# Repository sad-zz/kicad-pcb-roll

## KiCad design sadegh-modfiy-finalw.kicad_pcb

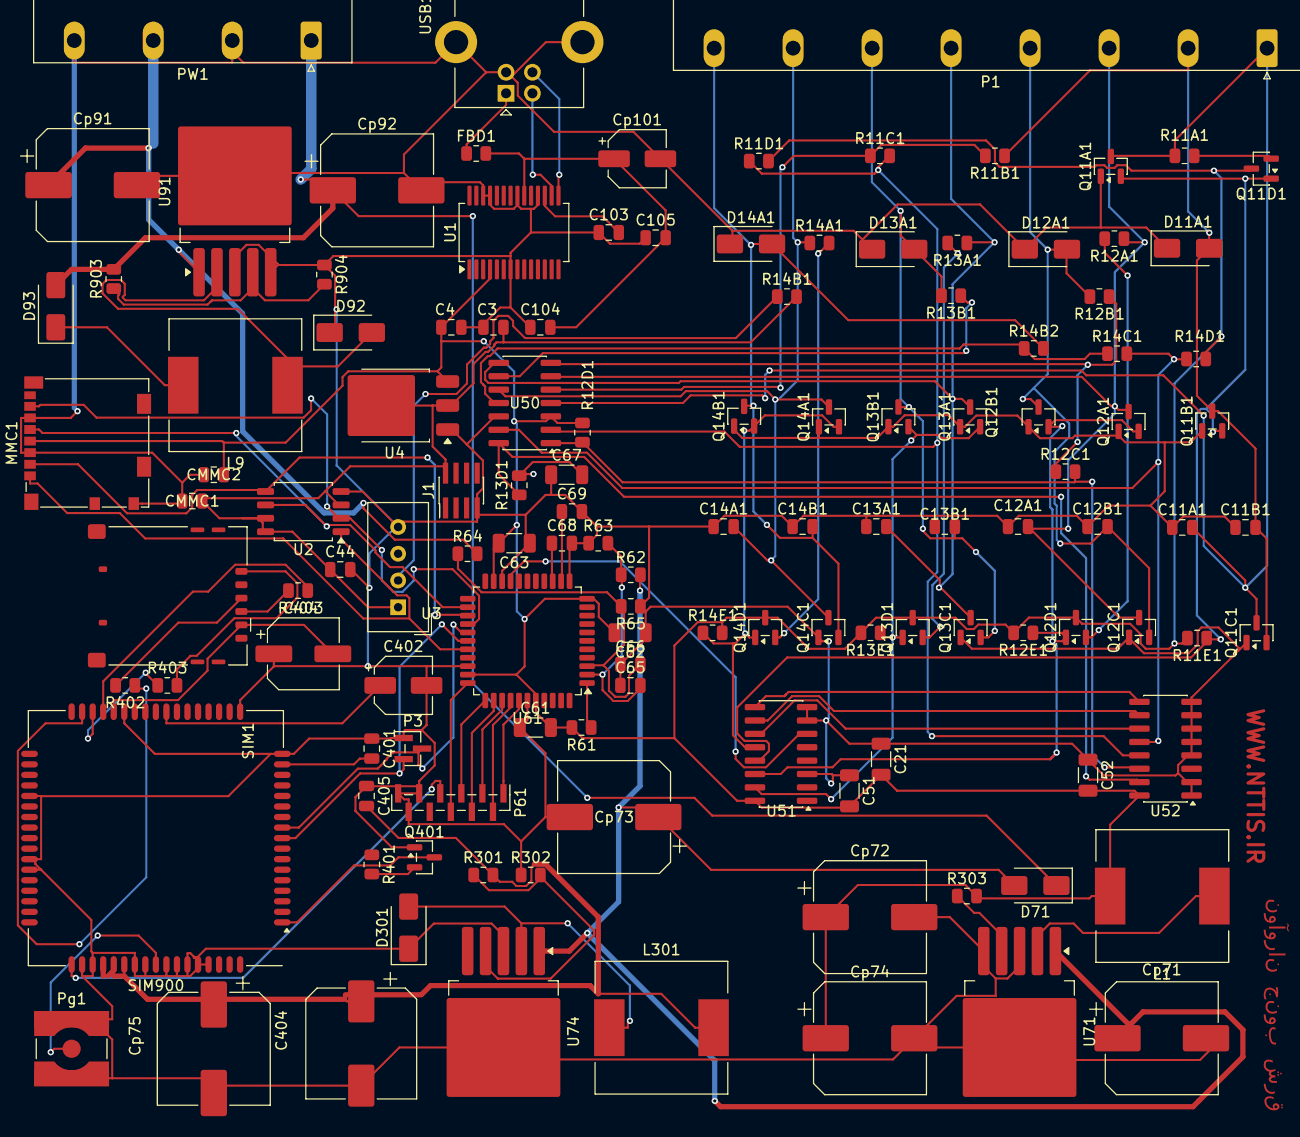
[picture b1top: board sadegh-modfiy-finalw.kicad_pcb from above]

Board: 2 copper layers, 124 parts (0 on the bottom side), 78 nets.

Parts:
C3, C4, C11A1, C11B1, C12A1, C12B1, C13A1, C13B1, C14A1, C14B1, C44, C65, C66, C68, C69, C103, C104, C105, C401, C405: Cap; C_0805_2012Metric
C21, C51, C52, C61, C62, C63, C67: Cap; C_1206_3216Metric
C402: Cap Pol1; CP_Elec_5x5.3
C403: Cap; CP_Elec_6.3x5.4
C404: Cap Pol1; CP_Elec_10x10
CMMC1, CMMC2: Cap; C_0805_2012Metric
Cp71, Cp72, Cp73, Cp74, Cp75, Cp91, Cp92: Cap Pol1; CP_Elec_10x12.5
Cp101: Cap Pol1; CP_Elec_5x5.3
D11A1, D12A1, D13A1, D14A1: 1N5819; D_SMA
D71: Diode 1N4007; D_SMA
D92, D301: Diode 1N5819; D_SMA
D93: Diode 1N4001; D_SMA
FBD1: Res1; R_0805_2012Metric
J1: Conn_02x04_Odd_Even; PinHeader_2x04_P1.00mm_Vertical_SMD
L1, L9, L301: Inductor Iron; L_12x12mm_H8mm
MMC1: MMC/SD; microSD_HC_Molex_104031-0811
P1: Header 8; PhoenixContact_GMSTBA_2,5_8-G_1x08_P7.50mm_Horizontal
P3: Header 3; PinHeader_1x03_P1.00mm_Vertical_SMD_Pin1Left
P61: Header 11; PinHeader_1x11_P1.00mm_Vertical_SMD_Pin1Left
PW1: Header 4; PhoenixContact_GMSTBA_2,5_4-G_1x04_P7.50mm_Horizontal
Pg1: SMB; SMA_Amphenol_132134-10_Vertical
Q11A1, Q11B1, Q11C1, Q12A1, Q12B1, Q12C1, Q13A1, Q13B1, Q13C1, Q14A1, Q14B1, Q14C1: 2N7000; SOT-23
Q11D1, Q12D1, Q13D1, Q14D1: 2SJ196/BSS92; SOT-23
Q401: 2N3904; SOT-23
R11A1, R11B1, R11C1, R11D1, R11E1, R12A1, R12B1, R12C1, R12D1, R12E1, R13A1, R13B1, R13D1, R13E1, R14A1, R14B1, R14B2, R14C1, R14D1, R14E1, R61, R62, R63, R64, R65, R301, R302, R303, R401, R903, R904: Res1; R_0805_2012Metric
R402, R403, R404: R_0805_2012Metric
SIM1: 6PIN SIMCARD; microSIM_JAE_SF53S006VCBR2000
SIM900: SIM900/SIM900A; SIMCom_SIM900
U1: UART<->USB; SSOP-28_5.3x10.2mm_P0.65mm
U2: W25Q32JVSS; SOIC-8_5.3x5.3mm_P1.27mm
U3: DHT11; Aosong_DHT11_5.5x12.0_P2.54mm
U4: AMS1117CD-3.3; TO-252-3_TabPin2
U50: LM339J; SOIC-14_3.9x8.7mm_P1.27mm
U51, U52: HCF4051BEY; SOIC-16_3.9x9.9mm_P1.27mm
U61: DSPIC30F4011-30I/P; TQFP-44_10x10mm_P0.8mm
U71, U74, U91: LM2576D2T-ADJ; TO-263-5_TabPin3
USB1: USB TYPEB; USB_B_Lumberg_2411_02_Horizontal

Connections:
/MISO: MMC1.7 (MISO), U2.2 (DO/IO_{1}), U61.26 (PGC/EMUC/U1RX/SDI1/SDA/RF2)
/MMCCS: MMC1.1 (CS), U2.1 (~CS), U61.29 (C1TX/RF1)
/MOSI: MMC1.2 (MOSI), U2.5 (DI/IO_{0}), U61.25 (PGD/EMUD/U1TX/SDO1/SCL/RF3)
/NetLight: P61.7, SIM900.52 (NETLIGHT)
/SCK: MMC1.5 (SCK), U2.6 (CLK), U61.24 (SCK1/RF6)
/SIM900_RXD: P3.2, SIM900.10 (RXD), U61.27 (U2TX/CN18/RF5)
/SIM900_TXD: P3.3, SIM900.9 (TXD), U61.28 (U2RX/CN17/RF4)
/loopselA: U51.11 (A), U52.11 (A)
/loopselB: U51.10 (B), U52.10 (B)
/loopselC: U51.9 (C), U52.9 (C)
GND: C3.1, C4.2, C11A1.1, C11B1.1, C12A1.1, C12B1.1, C13A1.1, C13B1.1, C14A1.1, C14B1.1, C21.1, C44.2, C51.1, C52.1, C61.1, C62.1, C63.1, C65.1, C66.1, C67.1, C68.2, C69.2, C103.1, C104.1, C105.1, C401.1, C402.2, C403.1, C404.2, C405.1, CMMC1.1, CMMC2.1, Cp71.2, Cp72.2, Cp73.2, Cp74.2, Cp75.2, Cp91.2, Cp92.2, Cp101.2, D11A1.1 (A), D12A1.1 (A), D13A1.1 (A), D14A1.1 (A), D92.1 (A), D301.1 (A), J1.7, MMC1.3 (GND), MMC1.6 (GND), MMC1.10 (HOLDER), P3.1, P61.9, P61.10, P61.11, PW1.2, PW1.4, Pg1.2 (Y), Q11A1.1 (E), Q11B1.1 (E), Q11C1.1 (E), Q12A1.1 (E), Q12B1.1 (E), Q12C1.1 (E), Q13A1.1 (E), Q13B1.1 (E), Q13C1.1 (E), Q14A1.1 (E), Q14B1.1 (E), Q14C1.1 (E), Q401.1 (E), R63.1, R65.1, R302.1, R904.1, SIM900.17 (GND), SIM900.18 (GND), SIM900.29 (GND), SIM900.39 (GND), SIM900.45 (GND), SIM900.46 (GND), SIM900.53 (GND), SIM900.54 (GND), SIM900.58 (GND), SIM900.59 (GND), SIM900.61 (GND), SIM900.62 (GND), SIM900.63 (GND), SIM900.64 (GND), SIM900.65 (GND), U1.7 (GND), U1.18 (GND), U1.21 (GND), U1.25 (AGND), U1.26 (TEST), U2.4 (GND), U3.4 (GND), U4.1 (GND), U50.12 (GND), U51.3 (IO_COM), U51.7 (GND), U51.8 (GND), U52.1 (IO_4), U52.2 (IO_6), U52.4 (IO_7), U52.5 (IO_5), U52.6 (INH), U52.7 (GND), U52.8 (GND), U61.12 (VSS), U61.20 (VSS), U61.31 (VSS), U61.39 (AVSS), U71.3 (GND), U71.5 (~ON/OFF), U74.3 (GND), U91.3 (GND), U91.5 (~ON/OFF), USB1.4 (GND), USB1.5 (HOLDER)
unnamed: C402.1, SIM900.25
unnamed: C11B1.2, D11A1.2 (K), P1.2, Q11B1.3 (C), Q11C1.2 (B), R11B1.1
unnamed: C12B1.2, D12A1.2 (K), P1.4, Q12B1.3 (C), Q12C1.2 (B), R12B1.2
unnamed: C13B1.2, D13A1.2 (K), P1.6, Q13B1.3 (C), Q13C1.2 (B), R13B1.2
unnamed: C14B1.2, D14A1.2 (K), P1.8, Q14B1.3 (C), Q14C1.2 (B), R14B2.2
unnamed: L1.1, U71.2 (OUT)
unnamed: D92.2 (K), L9.1, U91.2 (OUT)
unnamed: D93.1 (A), L9.2
unnamed: D301.2 (K), L301.1, U74.2 (OUT)
unnamed: C3.2, C44.1, CMMC1.2, J1.2, R14B1.2, U2.3 (~WP/IO_{2}), U2.7 (~HOLD/~RESET/IO_{3}), U2.8 (VCC), U3.1 (VDD), U4.2 (VO)
unnamed: Pg1.1 (X), SIM900.60 (RF_ANT)
unnamed: Q11A1.2 (B), Q11B1.2 (B), Q11D1.1 (G), R11E1.1, U51.13 (IO_0)
unnamed: C11A1.2, P1.1, Q11A1.3 (C), Q11C1.3 (C), R11A1.1, U50.4 (IN1-)
unnamed: Q11D1.2 (D), R11A1.2
unnamed: Q12A1.2 (B), Q12B1.2 (B), Q12D1.1 (G), R12E1.1, U51.14 (IO_1)
unnamed: C12A1.2, P1.3, Q12A1.3 (C), Q12C1.3 (C), R12A1.1, U50.6 (IN2-)
unnamed: Q12D1.2 (D), R12A1.2
unnamed: Q13A1.2 (B), Q13B1.2 (B), Q13D1.1 (G), R13E1.1, U51.15 (IO_2)
unnamed: C13A1.2, P1.5, Q13A1.3 (C), Q13C1.3 (C), R13A1.1, U50.8 (IN3-)
unnamed: Q13D1.2 (D), R13A1.2
unnamed: Q14A1.2 (B), Q14B1.2 (B), Q14D1.1 (G), R14E1.1, U51.12 (IO_3)
unnamed: C14A1.2, P1.7, Q14A1.3 (C), Q14C1.3 (C), R14A1.1, U50.10 (IN4-)
unnamed: Q14D1.2 (D), R14A1.2
unnamed: Q401.2 (B), R401.2
unnamed: Q401.3 (C), SIM900.1 (PWRKEY)
unnamed: R403.2, SIM1.3 (CLK)
unnamed: R404.2, SIM1.6 (IO)
unnamed: R402.2, SIM1.2 (RESET)
unnamed: C403.2, SIM1.1 (VCC), SIM900.30 (SIM_VDD)
unnamed: C401.2, SIM900.16 (NRESET)
unnamed: R403.1, SIM900.32 (SIM_CLK)
unnamed: R404.1, SIM900.31 (SIM_DATA)
unnamed: R402.1, SIM900.33 (SIM_RST)
unnamed: C103.2, U1.17 (3V3OUT)
unnamed: U1.16 (USBDM), USB1.2 (DN_(-))
unnamed: U1.15 (USBDP), USB1.3 (DP_(+))
unnamed: C104.2, C105.2, Cp101.1, FBD1.2, U1.20 (VCC)
unnamed: R14B1.1, U3.2 (DATA)
unnamed: R11B1.2, R11C1.1, U50.5 (IN1+)
unnamed: R11C1.2, R11D1.1, U50.2 (OUT1), U52.13 (IO_0)
unnamed: R12B1.1, R12C1.1, U50.7 (IN2+)
unnamed: R12C1.2, R12D1.1, U50.1 (OUT2), U52.14 (IO_1)
unnamed: R13B1.1, U50.9 (IN3+)
unnamed: R13D1.1, U50.14 (OUT3), U52.15 (IO_2)
unnamed: R14B2.1, R14C1.1, U50.11 (IN4+)
unnamed: R14C1.2, R14D1.1, U50.13 (OUT4), U52.12 (IO_3)
unnamed: U51.6 (INH), U61.19 (OC4/RD3)
unnamed: C66.2, R64.1, R65.2, U61.3 (EMUC3/AN1/VREF-/CN3/RB1)
unnamed: C65.2, R62.1, R63.2, U61.2 (EMUD3/AN0/VREF+/CN2/RB0)
unnamed: C69.1, U61.13 (OSC1/CLKI)
unnamed: C68.1, U61.14 (OSC2/CLKO/RC15)
unnamed: P61.2, U61.37 (PWM1H/RE1)
unnamed: P61.1, U61.38 (PWM1L/RE0)
unnamed: P61.4, U61.35 (PWM2H/RE3)
unnamed: P61.3, U61.36 (PWM2L/RE2)
unnamed: P61.6, U61.33 (PWM3H/RE5)
unnamed: P61.5, U61.34 (PWM3L/RE4)
unnamed: R61.1, U61.1 (~MCLR)
unnamed: R303.1, U71.4 (FB)
unnamed: R301.1, R302.2, U74.4 (FB)
unnamed: R903.1, R904.2, U91.4 (FB)
unnamed: FBD1.1, USB1.1 (VCC)
V12: Cp92.1, D71.1 (A), D93.2 (K), PW1.1, R903.2
VBAT: Cp71.1, Cp73.1, D71.2 (K), R62.2, U71.1 (VIN), U74.1 (VIN)
VCC: C4.1, C21.2, C51.2, C52.2, C61.2, C62.2, C63.2, C67.2, CMMC2.2, Cp72.1, Cp74.1, L1.2, MMC1.4 (VDD), Q11D1.3 (S), Q12D1.3 (S), Q13D1.3 (S), Q14D1.3 (S), R11D1.2, R11E1.2, R12D1.2, R12E1.2, R13D1.2, R13E1.2, R14D1.2, R14E1.2, R61.2, R303.2, U1.4 (VCCIO), U4.3 (VI), U50.3 (V+), U51.16 (VCC), U52.16 (VCC), U61.11 (VDD), U61.21 (VDD), U61.32 (VDD), U61.40 (AVDD)
VCC-SIM: C404.1, C405.2, Cp75.1, L301.2, R301.2, SIM900.55 (VBAT), SIM900.56 (VBAT), SIM900.57 (VBAT)
VSOL: Cp91.1, PW1.3, R64.2, U91.1 (VIN)
